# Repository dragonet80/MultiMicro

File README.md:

MultiMicro
==========

MultiMicro Trainer is an small, simple and affordable microcontroller trainer everyone can use.
Its size is 10x10 cm, so you can order at a cheap price on online pcb manufarurers.

It's intended to be universal with any microcontroller from 6 to 100 pins and 5, 3.3 and 1.8 V.

It is formed by three parts:
* Base Trainer. It is the main pcb. It has voltage regulators, space for small breadboard, 8 push-buttons, 8 leds, 2 potenciometers and a buzzer. Plus, all connectors and pinheaders.
* Microcontroller adapter. You can make any adapter for your favorite microcontroller. You plug it to Base Trainer thru a 3x30 pinhead connector.
* Add-on boards. To add functionality. Preferred size is in multiples of 5x5 cm, to better fit Base Trainer, but can be any size.

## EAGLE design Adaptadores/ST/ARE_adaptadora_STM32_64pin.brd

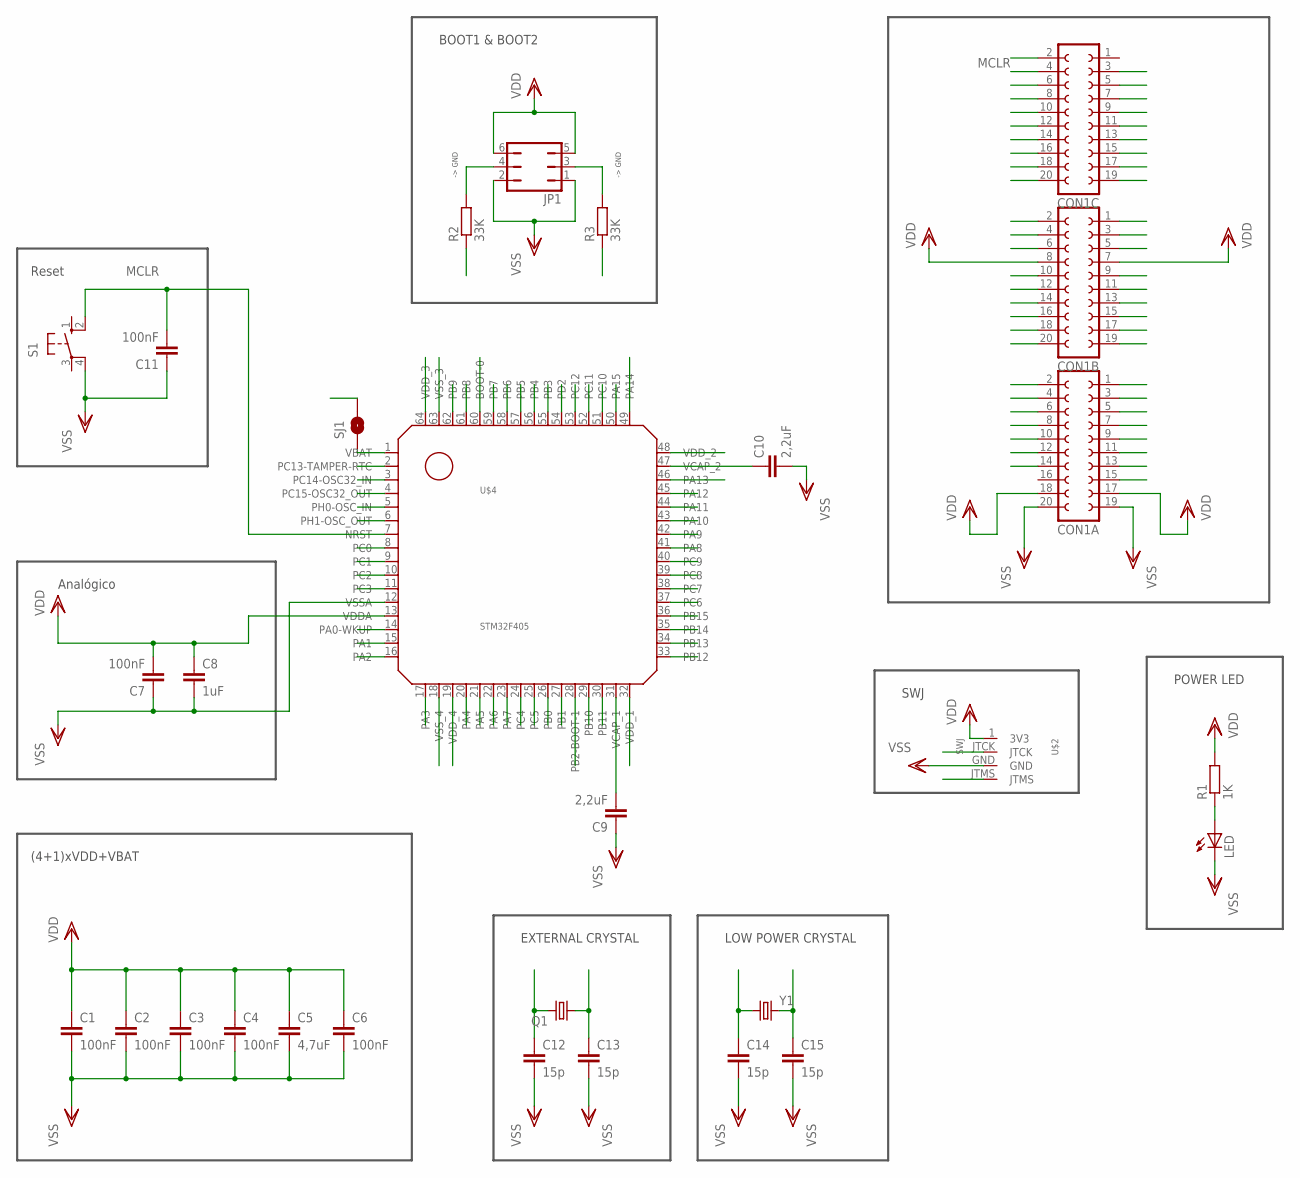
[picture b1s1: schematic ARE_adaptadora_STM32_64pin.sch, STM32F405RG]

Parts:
C1, C2, C3, C4, C6, C7, C11: 100nF; C0805K
C5: 4,7uF; C0805K
C8: 1uF; C0805K
C9, C10: 2,2uF; C0805K
C12, C13, C14, C15: 15p; C0805
CON1A, CON1B, CON1C: FE10-2W
JP1: JP3Q
LED: LEDCHIPLED_0805; CHIPLED_0805
Q1: CRYSTALHC18U-V; HC18U-V
R1: 1K; R0805
R2, R3: 33K; R0805
S1: 10-XX; B3F-10XX; MPN B3F-1000
SJ1: SOLDERJUMPERNO; SJ_2S-NO
U$2: SWJ
U$4: STM32F405; LQFP64
Y1: CRYSTAL32-SMD; CRYSTAL-32KHZ-SMD

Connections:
BOOT0: R2.1, U$4.60 (BOOT-0)
BOOT1: CON1B.3, R3.1, U$4.28 (PB2-BOOT-1)
JTCK: CON1A.3, U$2.JTCK, U$4.49 (PA14)
JTMS: CON1A.2, U$2.JTMS, U$4.46 (PA13)
MCLR: C11.2, CON1C.2, S1.2 (S1), U$4.7 (NRST)
unnamed: C10.1, U$4.47 (VCAP_2)
unnamed: C9.2, U$4.31 (VCAP_1)
unnamed: CON1C.4, U$4.2 (PC13-TAMPER-RTC)
unnamed: LED.A, R1.1
unnamed: CON1C.7, U$4.8 (PC0)
unnamed: CON1C.10, U$4.9 (PC1)
unnamed: CON1C.9, U$4.10 (PC2)
unnamed: CON1C.12, U$4.11 (PC3)
unnamed: CON1C.11, U$4.14 (PA0-WKUP)
unnamed: CON1C.14, U$4.15 (PA1)
unnamed: CON1C.13, U$4.16 (PA2)
unnamed: CON1C.16, U$4.17 (PA3)
unnamed: CON1C.15, U$4.20 (PA4)
unnamed: CON1C.18, U$4.21 (PA5)
unnamed: CON1C.17, U$4.22 (PA6)
unnamed: CON1C.20, U$4.23 (PA7)
unnamed: CON1C.19, U$4.24 (PC4)
unnamed: CON1B.2, U$4.25 (PC5)
unnamed: CON1B.1, U$4.26 (PB0)
unnamed: CON1B.4, U$4.27 (PB1)
unnamed: CON1B.6, U$4.29 (PB10)
unnamed: CON1B.5, U$4.30 (PB11)
unnamed: CON1B.9, U$4.33 (PB12)
unnamed: CON1B.10, U$4.34 (PB13)
unnamed: CON1B.11, U$4.35 (PB14)
unnamed: CON1B.12, U$4.36 (PB15)
unnamed: CON1B.13, U$4.37 (PC6)
unnamed: CON1B.14, U$4.38 (PC7)
unnamed: CON1B.15, U$4.39 (PC8)
unnamed: CON1B.16, U$4.40 (PC9)
unnamed: CON1B.17, U$4.41 (PA8)
unnamed: CON1B.18, U$4.42 (PA9)
unnamed: CON1B.19, U$4.43 (PA10)
unnamed: CON1B.20, U$4.44 (PA11)
unnamed: CON1A.1, U$4.45 (PA12)
unnamed: CON1A.4, U$4.50 (PA15)
unnamed: CON1A.5, U$4.51 (PC10)
unnamed: CON1A.6, U$4.52 (PC11)
unnamed: CON1A.7, U$4.53 (PC12)
unnamed: CON1A.8, U$4.54 (PD2)
unnamed: CON1A.9, U$4.55 (PB3)
unnamed: CON1A.10, U$4.56 (PB4)
unnamed: CON1A.11, U$4.57 (PB5)
unnamed: CON1A.12, U$4.58 (PB6)
unnamed: CON1A.13, U$4.59 (PB7)
unnamed: CON1A.14, U$4.61 (PB8)
unnamed: CON1A.15, U$4.62 (PB9)
unnamed: JP1.4, R2.2
unnamed: JP1.3, R3.2
P12OSC0: C13.1, CON1C.5, Q1.1, U$4.5 (PH0-OSC_IN)
P12OSC1: C12.1, CON1C.8, Q1.2, U$4.6 (PH1-OSC_OUT)
P12OSC320: C14.1, CON1C.3, U$4.3 (PC14-OSC32_IN), Y1.X1 (1)
P12OSC321: C15.1, CON1C.6, U$4.4 (PC15-OSC32_OUT), Y1.X2 (2)
VBAT: SJ1.1, U$4.1 (VBAT)
VDD: C1.1, C2.1, C3.1, C4.1, C5.1, C6.1, C7.2, C8.1, CON1A.17, CON1A.18, CON1B.7, CON1B.8, JP1.5, JP1.6, R1.2, SJ1.2, U$2.1 (3V3), U$4.13 (VDDA), U$4.19 (VDD_4), U$4.32 (VDD_1), U$4.48 (VDD_2), U$4.64 (VDD_3)
VSS: C1.2, C2.2, C3.2, C4.2, C5.2, C6.2, C7.1, C8.2, C9.1, C10.2, C11.1, C12.2, C13.2, C14.2, C15.2, CON1A.19, CON1A.20, JP1.1, JP1.2, LED.C, S1.4 (P1), U$2.GND, U$4.12 (VSSA), U$4.18 (VSS_4), U$4.63 (VSS_3)

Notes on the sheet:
(4+1)xVDD+VBAT
Reset
-> GND
BOOT1 & BOOT2
SWJ
Analógico
EXTERNAL CRYSTAL
POWER LED
LOW POWER CRYSTAL

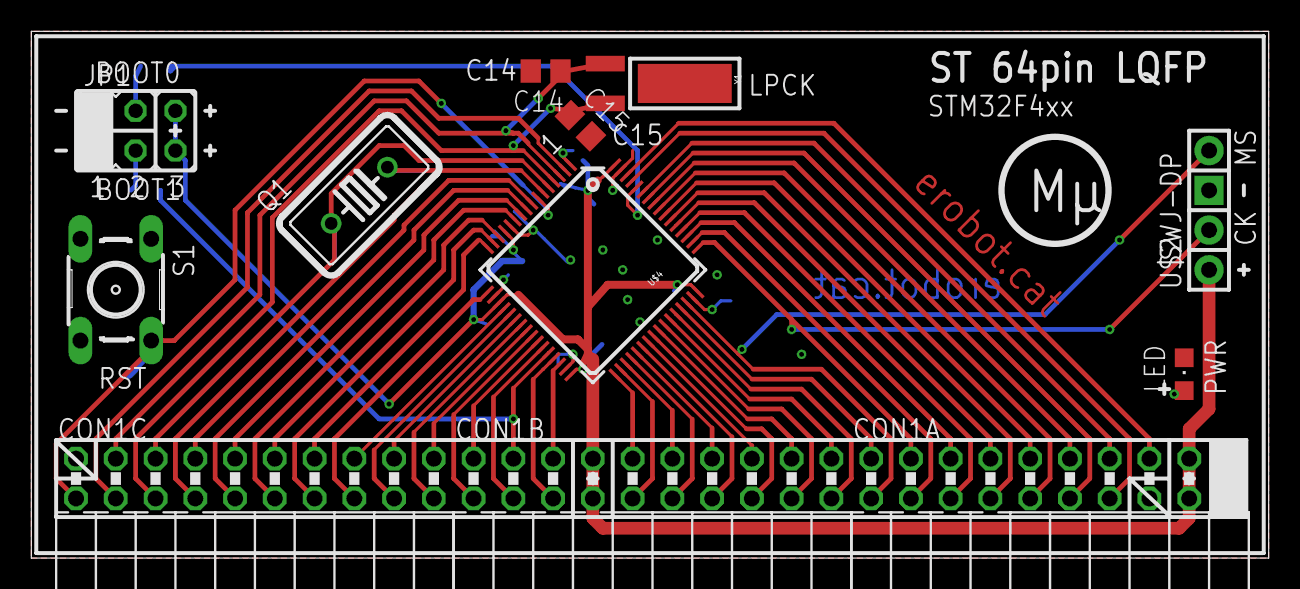
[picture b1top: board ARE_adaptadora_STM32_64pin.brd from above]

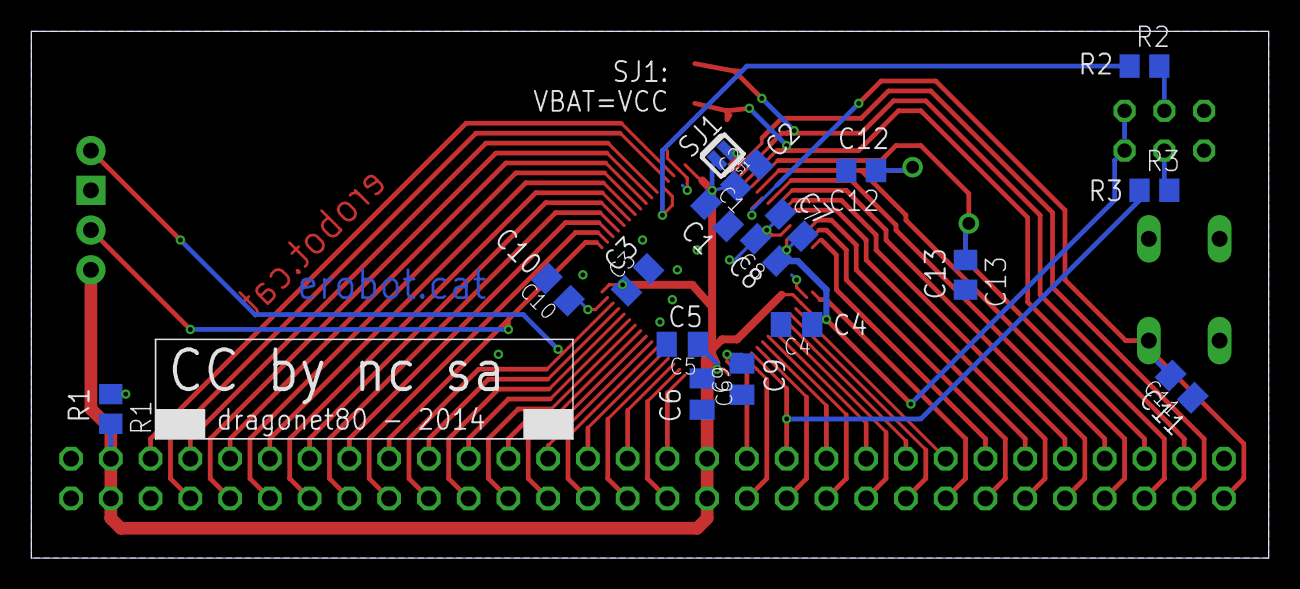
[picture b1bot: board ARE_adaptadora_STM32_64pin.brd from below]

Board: 2 copper layers, 79.1 x 33.7 mm, 29 parts (17 on the bottom side), 61 nets.

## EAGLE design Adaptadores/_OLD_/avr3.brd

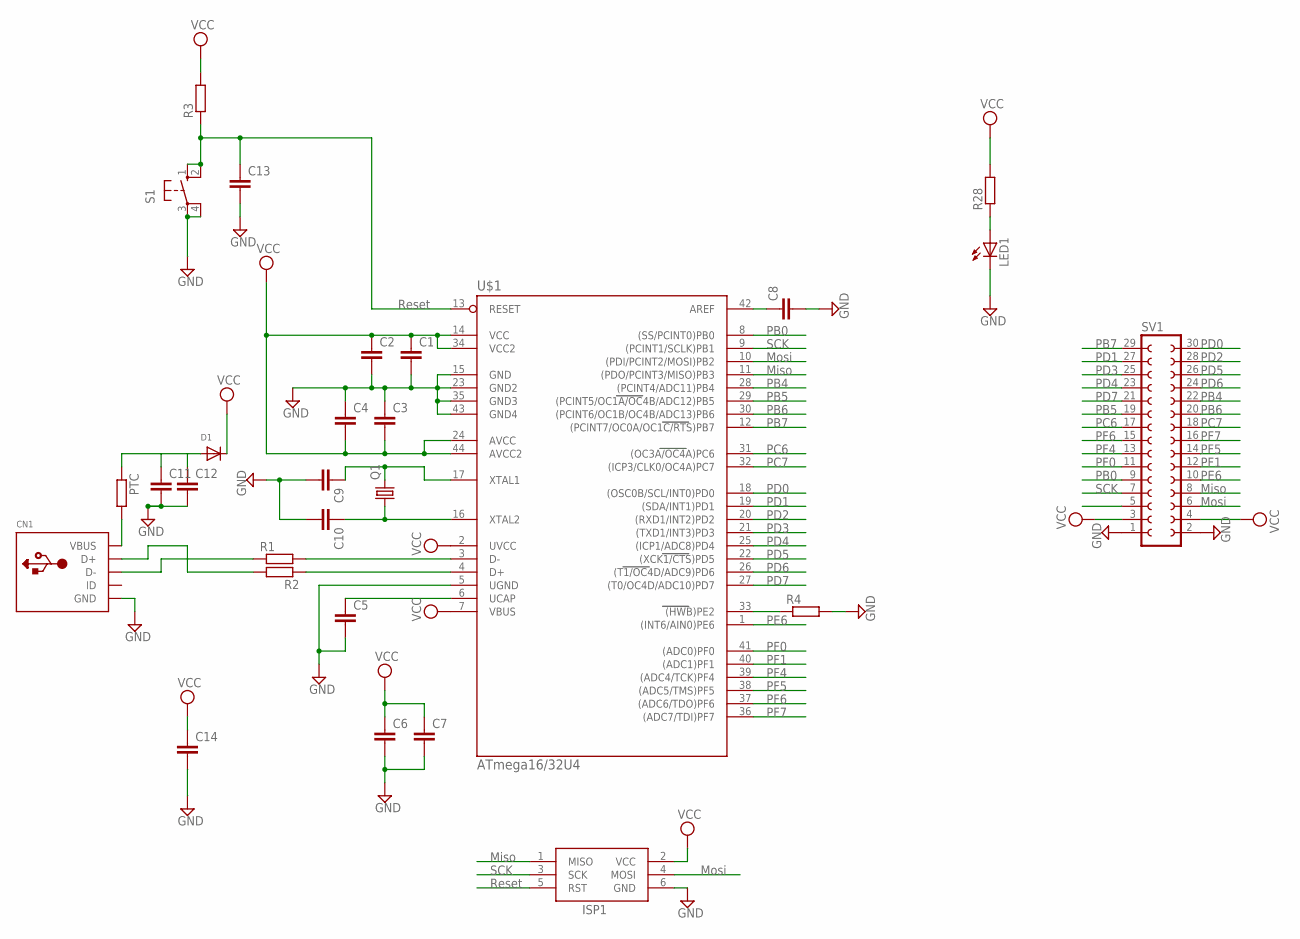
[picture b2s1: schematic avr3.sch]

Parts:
C1, C2, C3, C4, C5, C6, C7, C8, C9, C10, C11, C12, C13, C14: C-EUC1206; C1206
CN1: USBMINIB; USB-MINIB
D1: DIODESOD-123; SOD-123
ISP1: AVRISP-6; AVRISP
LED1: LEDCHIPLED_1206; CHIPLED_1206
PTC: R-EU_R1206; R1206
Q1: CRYSTALHC49UP; HC49UP
R1, R2, R3, R4, R28: R-EU_R1206; R1206
S1: 10-XX; B3F-10XX
SV1: FE15-2
U$1: ATmega16/32U4; TQFP44

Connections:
GND: C1.2, C2.2, C3.1, C4.1, C5.2, C6.2, C7.2, C8.2, C9.2, C10.2, C11.2, C12.2, C13.2, C14.2, CN1.GND, ISP1.6 (GND), LED1.C, R4.2, S1.3, S1.4 (P1), SV1.1, SV1.2, U$1.5 (UGND), U$1.15 (GND), U$1.23 (GND2), U$1.35 (GND3), U$1.43 (GND4)
MISO: ISP1.1 (MISO), SV1.8, U$1.11 ((PDO/PCINT3/MISO)PB3)
MOSI: ISP1.4 (MOSI), SV1.6, U$1.10 ((PDI/PCINT2/MOSI)PB2)
unnamed: C9.1, Q1.2, U$1.17 (XTAL1)
unnamed: C10.1, Q1.1, U$1.16 (XTAL2)
unnamed: C5.1, U$1.6 (UCAP)
unnamed: R4.1, U$1.33 ((HWB)PE2)
unnamed: R2.1, U$1.4 (D+)
unnamed: R1.2, U$1.3 (D-)
unnamed: CN1.D+, R2.2
unnamed: CN1.D-, R1.1
unnamed: CN1.VBUS, PTC.2
unnamed: C11.1, C12.1, D1.A, PTC.1
unnamed: C8.1, U$1.42 (AREF)
unnamed: LED1.A, R28.1
PB0: SV1.9, U$1.8 ((SS/PCINT0)PB0)
PB4: SV1.22, U$1.28 ((PCINT4/ADC11)PB4)
PB5: SV1.19, U$1.29 ((PCINT5/OC1A/OC4B/ADC12)PB5)
PB6: SV1.20, U$1.30 ((PCINT6/OC1B/OC4B/ADC13)PB6)
PB7: SV1.29, U$1.12 ((PCINT7/OC0A/OC1C/RTS)PB7)
PC6: SV1.17, U$1.31 ((OC3A/OC4A)PC6)
PC7: SV1.18, U$1.32 ((ICP3/CLK0/OC4A)PC7)
PD0: SV1.30, U$1.18 ((OSC0B/SCL/INT0)PD0)
PD1: SV1.27, U$1.19 ((SDA/INT1)PD1)
PD2: SV1.28, U$1.20 ((RXD1/INT2)PD2)
PD3: SV1.25, U$1.21 ((TXD1/INT3)PD3)
PD4: SV1.23, U$1.25 ((ICP1/ADC8)PD4)
PD5: SV1.26, U$1.22 ((XCK1/CTS)PD5)
PD6: SV1.24, U$1.26 ((T1/OC4D/ADC9)PD6)
PD7: SV1.21, U$1.27 ((T0/OC4D/ADC10)PD7)
PE6: SV1.10, U$1.1 ((INT6/AIN0)PE6)
PF0: SV1.11, U$1.41 ((ADC0)PF0)
PF1: SV1.12, U$1.40 ((ADC1)PF1)
PF4: SV1.13, U$1.39 ((ADC4/TCK)PF4)
PF5: SV1.14, U$1.38 ((ADC5/TMS)PF5)
PF6: SV1.15, U$1.37 ((ADC6/TDO)PF6)
PF7: SV1.16, U$1.36 ((ADC7/TDI)PF7)
RESET: C13.1, ISP1.5 (RST), R3.1, S1.1 (S), S1.2 (S1), U$1.13 (RESET)
SCK: ISP1.3 (SCK), SV1.7, U$1.9 ((PCINT1/SCLK)PB1)
VCC: C1.1, C2.1, C3.2, C4.2, C6.1, C7.1, C14.1, D1.C, ISP1.2 (VCC), R3.2, R28.2, SV1.3, SV1.4, U$1.2 (UVCC), U$1.7 (VBUS), U$1.14 (VCC), U$1.24 (AVCC), U$1.34 (VCC2), U$1.44 (AVCC2)

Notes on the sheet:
Reset
Miso
Mosi
SCK
PB7
PB6
PB5
PB4
PB0
PC6
PC7
PD0
PD1
PD2
PD3
PD4
PD5
PD6
PD7
PE6
PF0
PF1
PF4
PF5
PF6
PF7

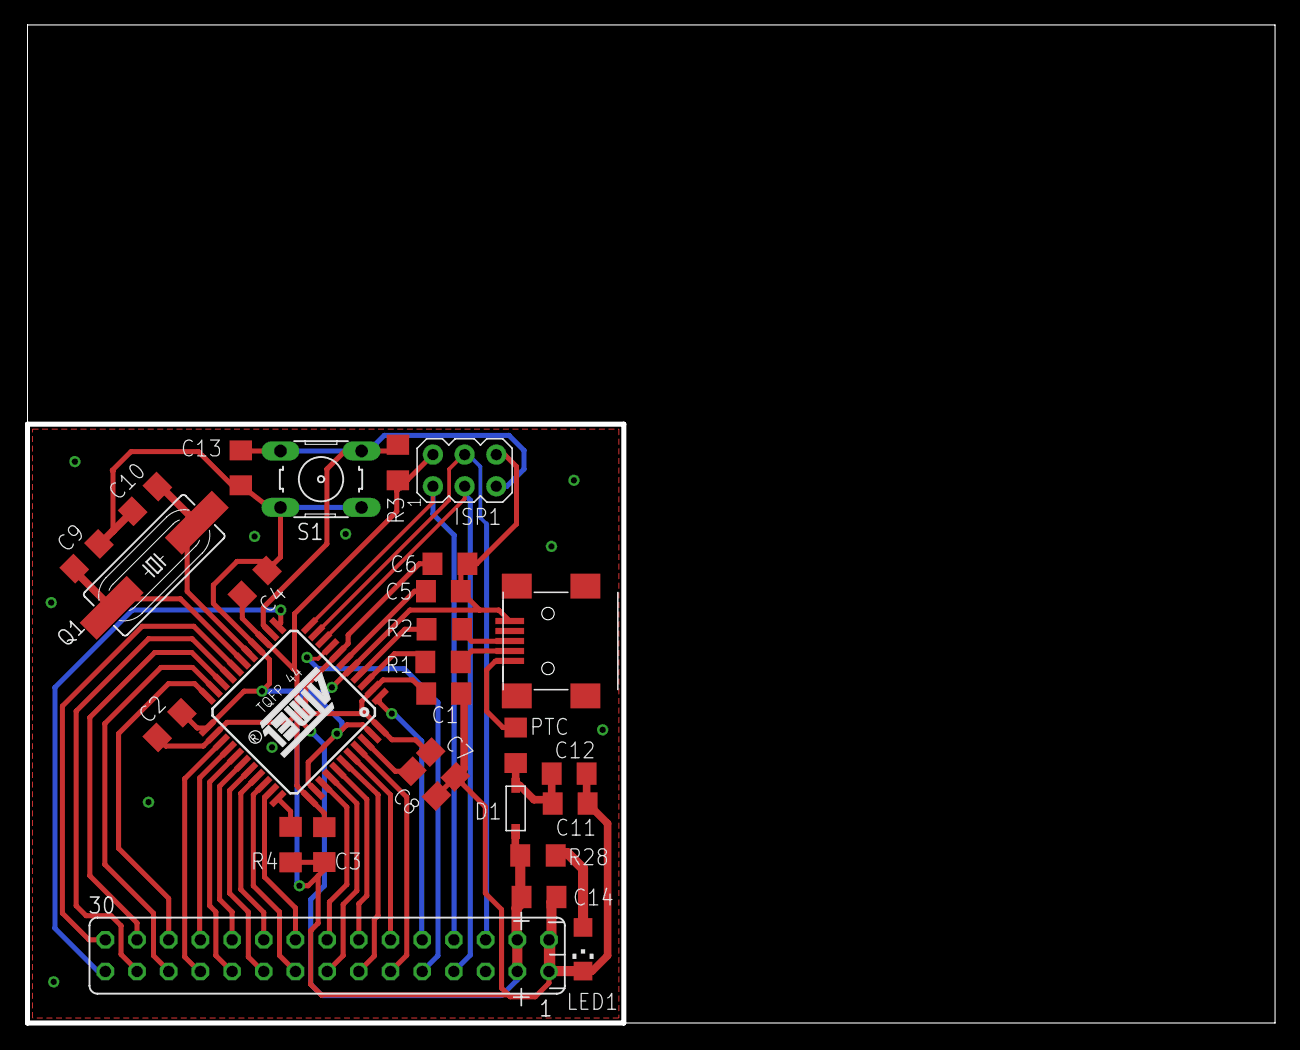
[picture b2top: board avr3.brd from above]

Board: 2 copper layers, 100.0 x 80.0 mm, 28 parts (0 on the bottom side), 40 nets.

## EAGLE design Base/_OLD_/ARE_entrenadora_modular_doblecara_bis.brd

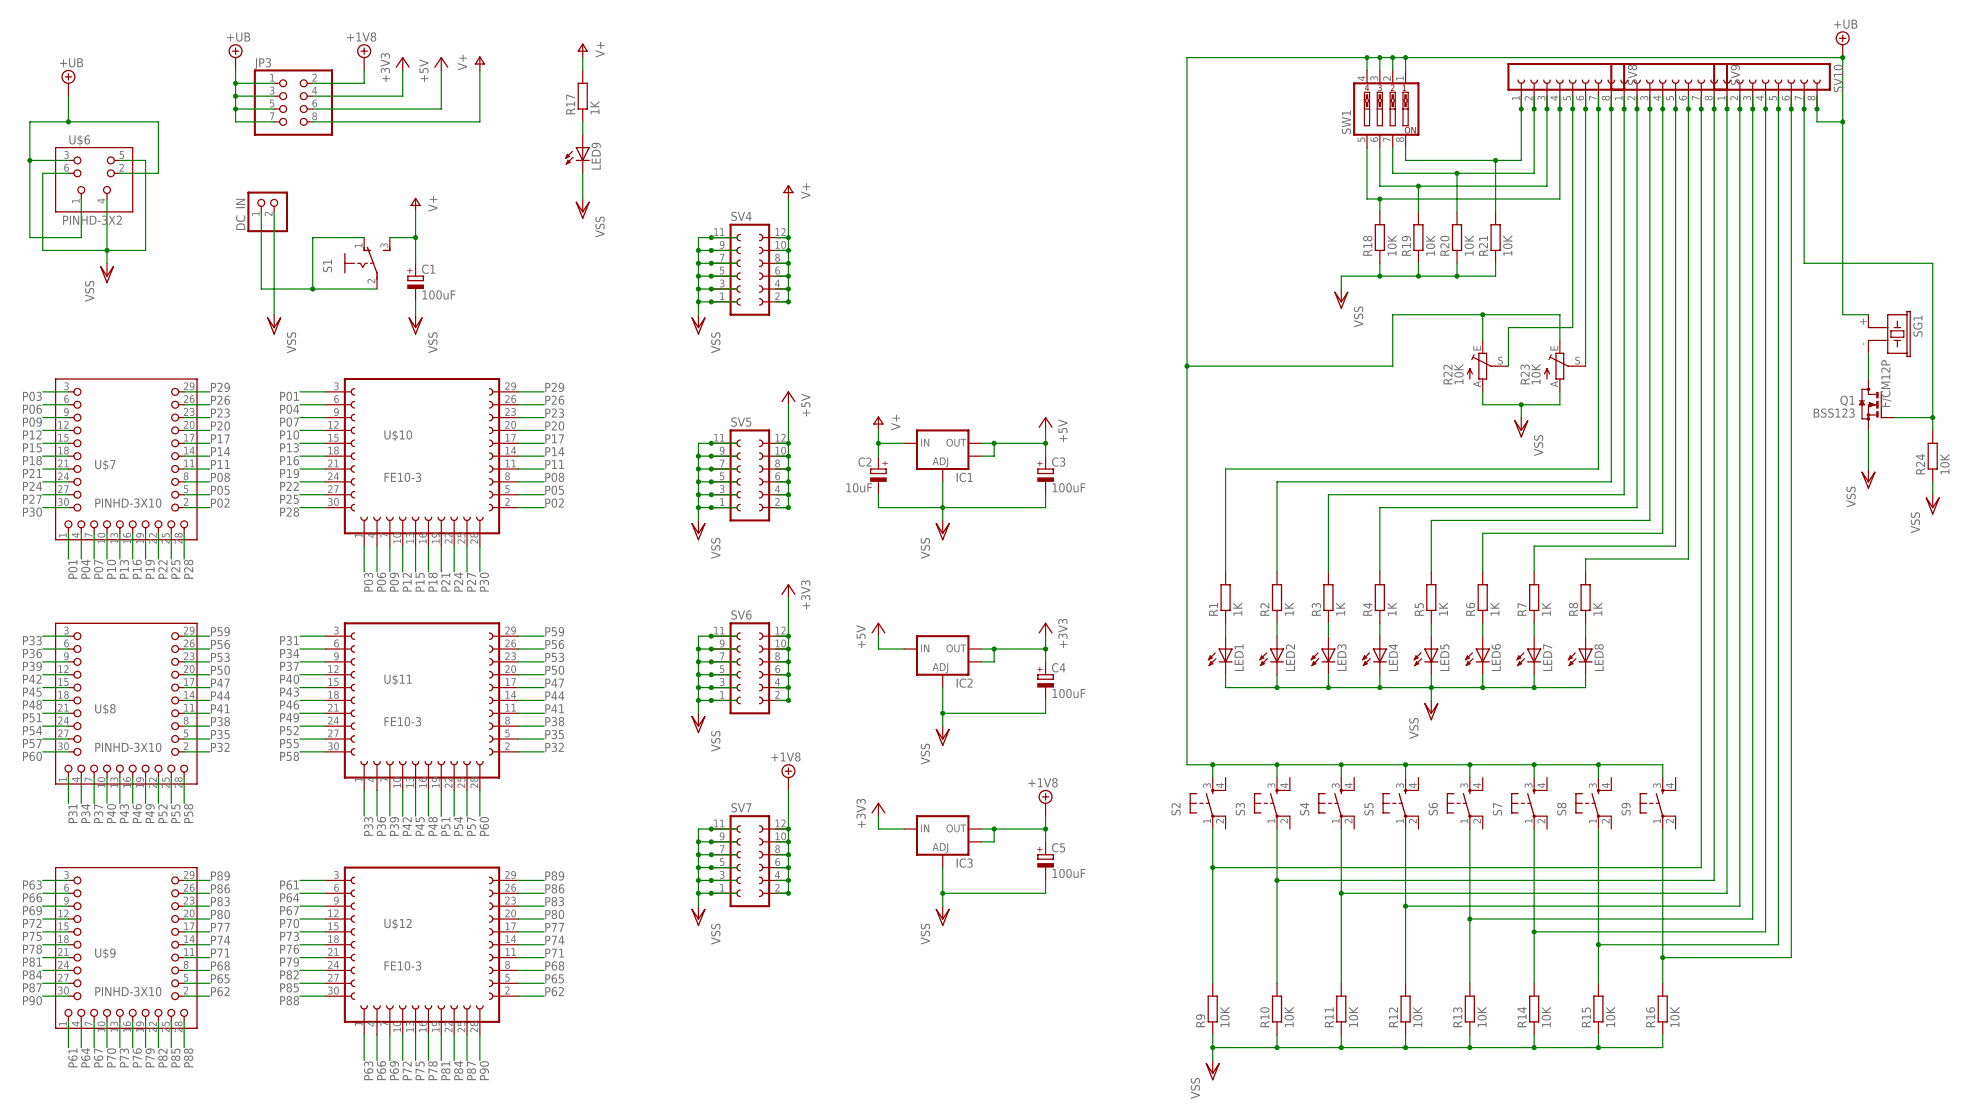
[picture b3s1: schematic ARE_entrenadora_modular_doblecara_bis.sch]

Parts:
C1: 100uF; E2,5-6
C2: 10uF; SMC_C
C3, C4, C5: 100uF; CT7343
DC_IN: PINHD-1X2/90; 1X02/90
IC1, IC2, IC3: V_REG_LM1117SOT223; SOT223
JP3: PINHD-2X4; 2X04
LED1, LED2, LED3, LED4, LED5, LED6, LED7, LED8, LED9: LEDCHIP-LED0805; CHIP-LED0805
Q1: BSS123; SOT23
R1, R2, R3, R4, R5, R6, R7, R8, R17: 1K; R0805
R9, R10, R11, R12, R13, R14, R15, R16, R18, R19, R20, R21, R24: 10K; R0805
R22, R23: 10K; CA6V
S1: 255SB
S2, S3, S4, S5, S6, S7, S8, S9: TAC_SWITCHPTH; TACTILE-PTH
SG1: F/CM12P
SV4, SV5, SV6, SV7: FE06-2
SV8, SV9, SV10: FE08-1; FE08
SW1: SW_DIP-4; EDG-04
U$6: PINHD-3X2; 3X02/90
U$7, U$8, U$9: PINHD-3X10; 3X10/90
U$10, U$11, U$12: FE10-3

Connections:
+3V3: C4.+, IC2.2 (OUT), IC2.4 (OUT), IC3.3 (IN), JP3.4, SV6.2, SV6.4, SV6.6, SV6.8, SV6.10, SV6.12
+5V: C3.+, IC1.2 (OUT), IC1.4 (OUT), IC2.3 (IN), JP3.6, SV5.2, SV5.4, SV5.6, SV5.8, SV5.10, SV5.12
+18V: C5.+, IC3.2 (OUT), IC3.4 (OUT), JP3.2, SV7.2, SV7.4, SV7.6, SV7.8, SV7.10, SV7.12
+UB: JP3.1, JP3.3, JP3.5, JP3.7, R22.E, R23.E, S2.3, S3.3, S4.3, S5.3, S6.3, S7.3, S8.3, S9.3, SG1.+ (1), SV10.8, SW1.1, SW1.2, SW1.3, SW1.4, U$6.1, U$6.2, U$6.3
unnamed: LED1.A, R1.1
unnamed: LED2.A, R2.1
unnamed: LED3.A, R3.1
unnamed: LED4.A, R4.1
unnamed: R2.2, SV8.8
unnamed: R3.2, SV9.1
unnamed: R1.2, SV8.7
unnamed: R4.2, SV9.2
unnamed: LED9.A, R17.1
unnamed: Q1.3 (D), SG1.- (2)
unnamed: DC_IN.1, S1.1 (O), S1.2
unnamed: LED5.A, R5.1
unnamed: LED6.A, R6.1
unnamed: LED7.A, R7.1
unnamed: LED8.A, R8.1
unnamed: R9.2, S2.1, SV9.7
unnamed: R10.2, S3.1, SV9.8
unnamed: R11.2, S4.1, SV10.1
unnamed: R12.2, S5.1, SV10.2
unnamed: R13.2, S6.1, SV10.3
unnamed: R14.2, S7.1, SV10.4
unnamed: R15.2, S8.1, SV10.5
unnamed: R16.2, S9.1, SV10.6
unnamed: Q1.1 (G), R24.2, SV10.7
unnamed: R23.S, SV8.6
unnamed: R22.S, SV8.5
unnamed: R6.2, SV9.4
unnamed: R7.2, SV9.5
unnamed: R5.2, SV9.3
unnamed: R8.2, SV9.6
unnamed: R18.2, SV8.4, SW1.5
unnamed: R19.2, SV8.3, SW1.6
unnamed: R20.2, SV8.2, SW1.7
unnamed: R21.2, SV8.1, SW1.8
P01: U$7.1, U$10.3
P02: U$7.2, U$10.2
P03: U$7.3, U$10.1
P04: U$7.4, U$10.6
P05: U$7.5, U$10.5
P06: U$7.6, U$10.4
P07: U$7.7, U$10.9
P08: U$7.8, U$10.8
P09: U$7.9, U$10.7
P10: U$7.10, U$10.12
P11: U$7.11, U$10.11
P12: U$7.12, U$10.10
P13: U$7.13, U$10.15
P14: U$7.14, U$10.14
P15: U$7.15, U$10.13
P16: U$7.16, U$10.18
P17: U$7.17, U$10.17
P18: U$7.18, U$10.16
P19: U$7.19, U$10.21
P20: U$7.20, U$10.20
P21: U$7.21, U$10.19
P22: U$7.22, U$10.24
P23: U$7.23, U$10.23
P24: U$7.24, U$10.22
P25: U$7.25, U$10.27
P26: U$7.26, U$10.26
P27: U$7.27, U$10.25
P28: U$7.28, U$10.30
P29: U$7.29, U$10.29
P30: U$7.30, U$10.28
P31: U$8.1, U$11.3
P32: U$8.2, U$11.2
P33: U$8.3, U$11.1
P34: U$8.4, U$11.6
P35: U$8.5, U$11.5
P36: U$8.6, U$11.4
P37: U$8.7, U$11.9
P38: U$8.8, U$11.8
P39: U$8.9, U$11.7
P40: U$8.10, U$11.12
P41: U$8.11, U$11.11
P42: U$8.12, U$11.10
P43: U$8.13, U$11.15
P44: U$8.14, U$11.14
P45: U$8.15, U$11.13
P46: U$8.16, U$11.18
P47: U$8.17, U$11.17
P48: U$8.18, U$11.16
P49: U$8.19, U$11.21
P50: U$8.20, U$11.20
P51: U$8.21, U$11.19
P52: U$8.22, U$11.24
P53: U$8.23, U$11.23
P54: U$8.24, U$11.22
P55: U$8.25, U$11.27
P56: U$8.26, U$11.26
P57: U$8.27, U$11.25
P58: U$8.28, U$11.30
P59: U$8.29, U$11.29
P60: U$8.30, U$11.28
P61: U$9.1, U$12.3
P62: U$9.2, U$12.2
P63: U$9.3, U$12.1
P64: U$9.4, U$12.6
P65: U$9.5, U$12.5
P66: U$9.6, U$12.4
P67: U$9.7, U$12.9
P68: U$9.8, U$12.8
P69: U$9.9, U$12.7
P70: U$9.10, U$12.12
P71: U$9.11, U$12.11
P72: U$9.12, U$12.10
P73: U$9.13, U$12.15
P74: U$9.14, U$12.14
P75: U$9.15, U$12.13
P76: U$9.16, U$12.18
P77: U$9.17, U$12.17
P78: U$9.18, U$12.16
P79: U$9.19, U$12.21
P80: U$9.20, U$12.20
P81: U$9.21, U$12.19
P82: U$9.22, U$12.24
P83: U$9.23, U$12.23
P84: U$9.24, U$12.22
P85: U$9.25, U$12.27
P86: U$9.26, U$12.26
P87: U$9.27, U$12.25
P88: U$9.28, U$12.30
P89: U$9.29, U$12.29
P90: U$9.30, U$12.28
V+: C1.+, C2.+, IC1.3 (IN), JP3.8, R17.2, S1.3 (S), SV4.2, SV4.4, SV4.6, SV4.8, SV4.10, SV4.12
VSS: C1.-, C2.-, C3.-, C4.-, C5.-, DC_IN.2, IC1.1 (ADJ), IC2.1 (ADJ), IC3.1 (ADJ), LED1.C, LED2.C, LED3.C, LED4.C, LED5.C, LED6.C, LED7.C, LED8.C, LED9.C, Q1.2 (S), R9.1, R10.1, R11.1, R12.1, R13.1, R14.1, R15.1, R16.1, R18.1, R19.1, R20.1, R21.1, R22.A, R23.A, R24.1, SV4.1, SV4.3, SV4.5, SV4.7, SV4.9, SV4.11, SV5.1, SV5.3, SV5.5, SV5.7, SV5.9, SV5.11, SV6.1, SV6.3, SV6.5, SV6.7, SV6.9, SV6.11, SV7.1, SV7.3, SV7.5, SV7.7, SV7.9, SV7.11, U$6.4, U$6.5, U$6.6

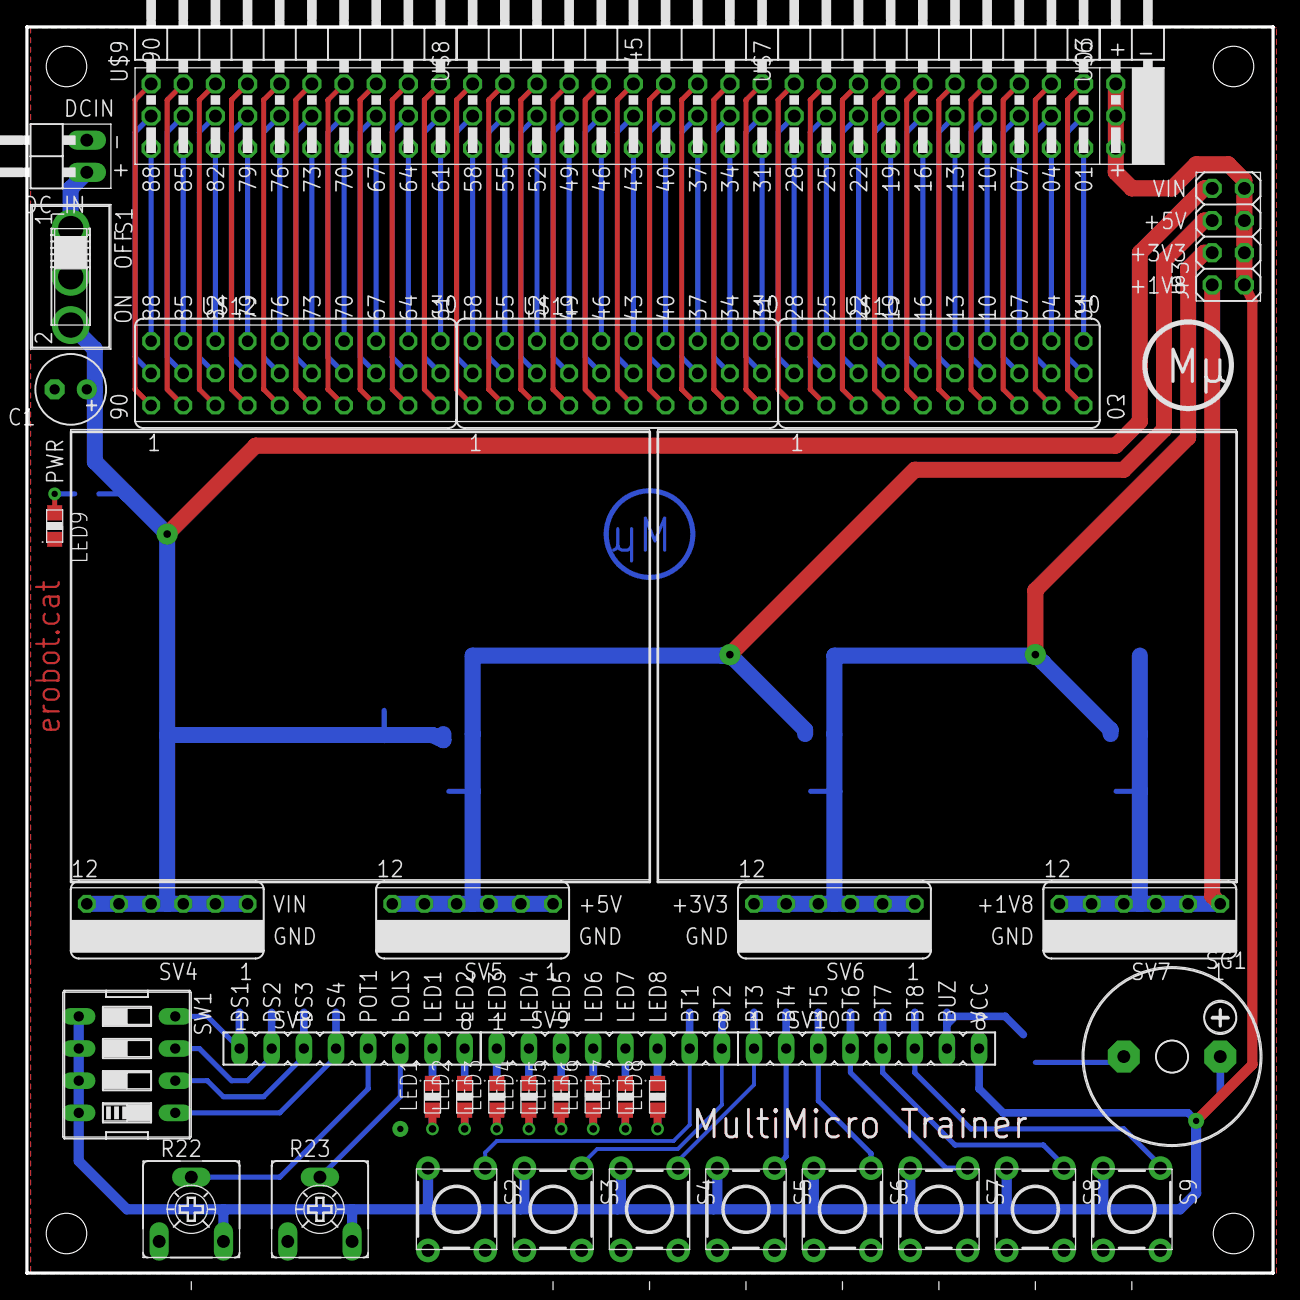
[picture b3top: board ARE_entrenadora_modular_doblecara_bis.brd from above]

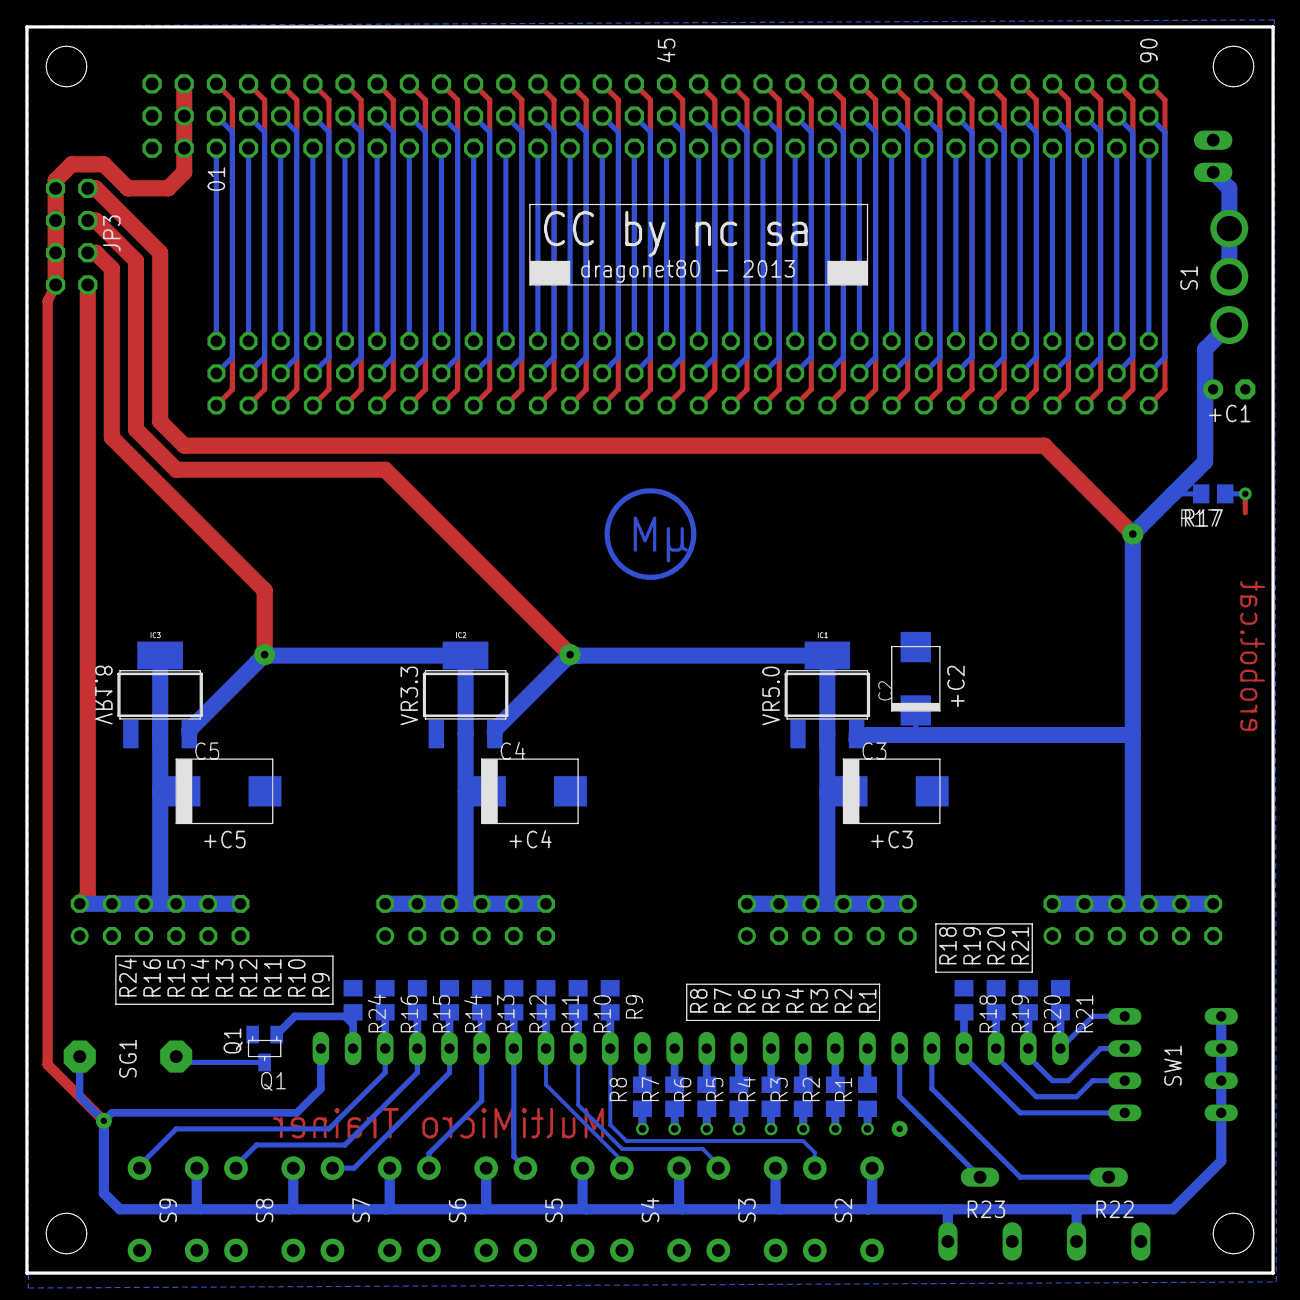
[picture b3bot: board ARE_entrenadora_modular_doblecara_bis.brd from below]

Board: 2 copper layers, 98.4 x 98.4 mm, 71 parts (30 on the bottom side), 130 nets.

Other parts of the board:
U$2, U$3: BREADBOARDMINI; BREADBOARD-MINI

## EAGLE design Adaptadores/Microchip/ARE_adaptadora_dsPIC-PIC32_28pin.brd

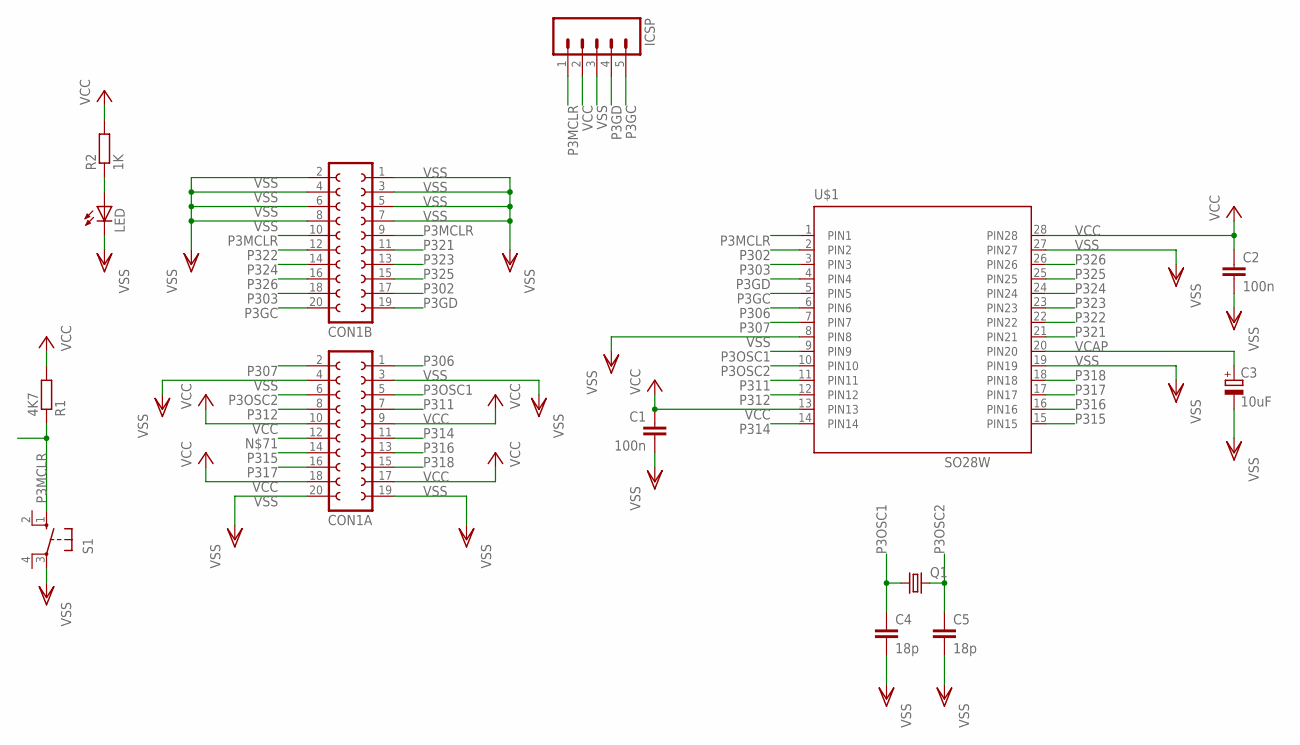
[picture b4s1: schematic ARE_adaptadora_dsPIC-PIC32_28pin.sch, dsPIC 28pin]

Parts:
C1, C2: 100n; C0805
C3: 10uF; SMC_C
C4, C5: 18p; C0805
CON1A, CON1B: FE10-2W
ICSP: M05PTH; 1X05
LED: LEDCHIPLED_0805; CHIPLED_0805
Q1: CRYSTALHC18U-V; HC18U-V
R1: 4K7; R0805
R2: 1K; R0805
S1: 10-XX; B3F-10XX; MPN B3F-1000
U$1: SO28W

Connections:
unnamed: LED.A, R2.1
P3GC: CON1B.20, ICSP.5, U$1.5 (PIN5)
P3GD: CON1B.19, ICSP.4, U$1.4 (PIN4)
P3MCLR: CON1B.9, CON1B.10, ICSP.1, R1.1, S1.1 (S), U$1.1 (PIN1)
P3OSC1: C4.1, CON1A.5, Q1.1, U$1.9 (PIN9)
P3OSC2: C5.1, CON1A.6, Q1.2, U$1.10 (PIN10)
P302: CON1B.17, U$1.2 (PIN2)
P303: CON1B.18, U$1.3 (PIN3)
P306: CON1A.1, U$1.6 (PIN6)
P307: CON1A.2, U$1.7 (PIN7)
P311: CON1A.7, U$1.11 (PIN11)
P312: CON1A.8, U$1.12 (PIN12)
P314: CON1A.11, U$1.14 (PIN14)
P315: CON1A.14, U$1.15 (PIN15)
P316: CON1A.13, U$1.16 (PIN16)
P317: CON1A.16, U$1.17 (PIN17)
P318: CON1A.15, U$1.18 (PIN18)
P321: CON1B.11, U$1.21 (PIN21)
P322: CON1B.12, U$1.22 (PIN22)
P323: CON1B.13, U$1.23 (PIN23)
P324: CON1B.14, U$1.24 (PIN24)
P325: CON1B.15, U$1.25 (PIN25)
P326: CON1B.16, U$1.26 (PIN26)
VCAP: C3.+, U$1.20 (PIN20)
VCC: C1.1, C2.1, CON1A.9, CON1A.10, CON1A.17, CON1A.18, ICSP.2, R1.2, R2.2, U$1.13 (PIN13), U$1.28 (PIN28)
VSS: C1.2, C2.2, C3.-, C4.2, C5.2, CON1A.3, CON1A.4, CON1A.19, CON1A.20, CON1B.1, CON1B.2, CON1B.3, CON1B.4, CON1B.5, CON1B.6, CON1B.7, CON1B.8, ICSP.3, LED.C, S1.3, U$1.8 (PIN8), U$1.19 (PIN19), U$1.27 (PIN27)

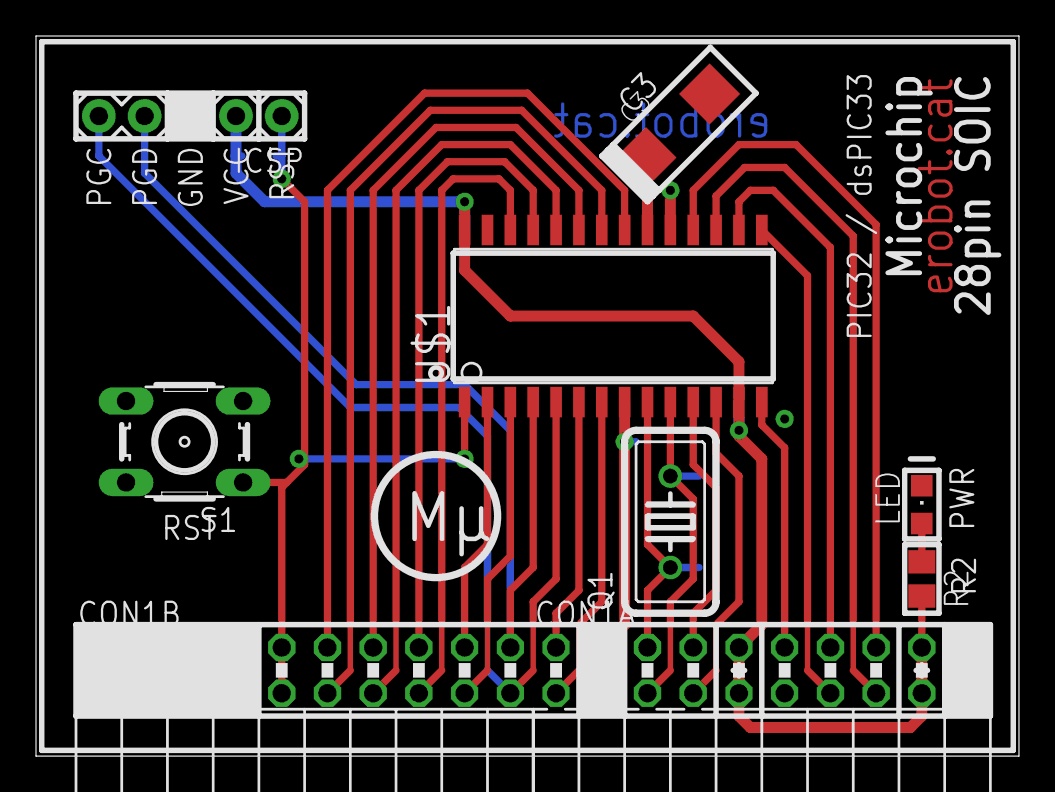
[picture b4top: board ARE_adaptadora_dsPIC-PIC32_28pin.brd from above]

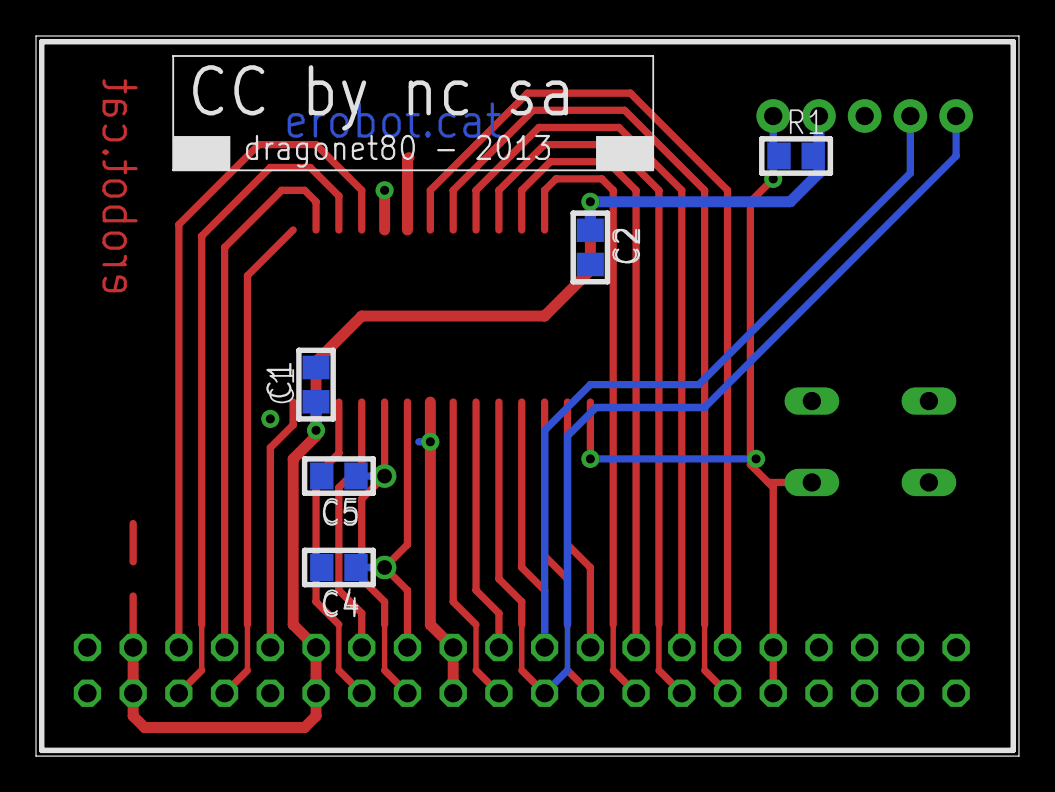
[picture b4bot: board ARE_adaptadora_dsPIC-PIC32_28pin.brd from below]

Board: 2 copper layers, 54.6 x 40.0 mm, 14 parts (5 on the bottom side), 26 nets.

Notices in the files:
Adaptadores/Atmel/ARE_adaptadora_AT90-8515_40pin.brd:
CC by nc sa
parts and their libraries:
SparkFun-Passives: Licensing: CC v3.0 Share-Alike You are welcome to use this library for commercial purposes.
SparkFun-FreqCtrl: Licensing: Creative Commons ShareAlike 4.0 International - https://creativecommons.org/licenses/by-sa/4.0
